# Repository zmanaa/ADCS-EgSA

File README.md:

# ADCS-EgSA
Attitude Determination Control Subsystem project. This project was under supervision of Egyptian Space Agency.

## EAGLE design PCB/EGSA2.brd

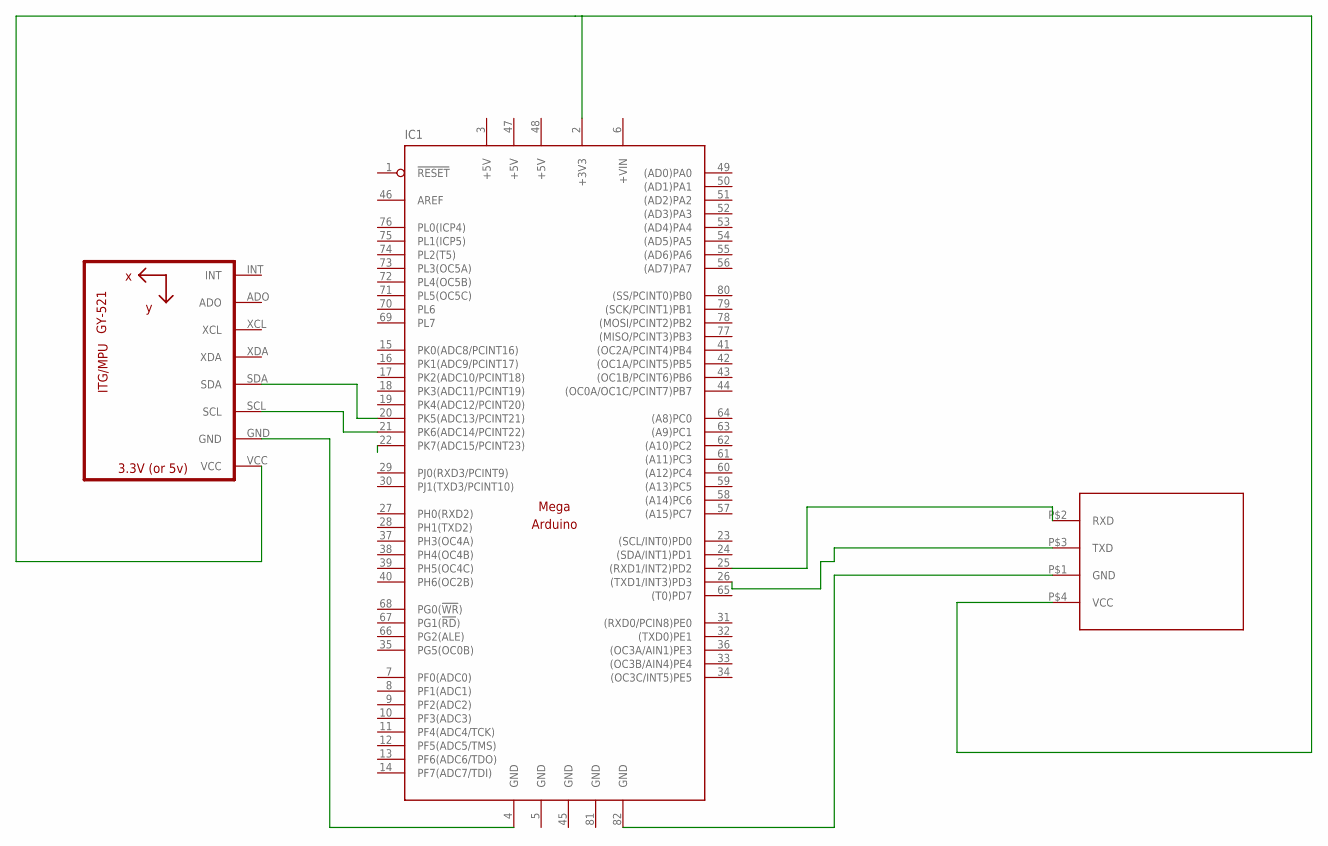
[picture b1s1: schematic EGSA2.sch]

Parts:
IC1: MEGAARDUINO_11; MEGA_ARDUINO_1
U1: GY-521MPU6050; GY-521
U$2: HC-06

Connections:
+5V: IC1.3 (+5V), IC1.47 (+5V), IC1.48 (+5V)
+VIN: IC1.6 (+VIN)
GND: IC1.5 (GND), IC1.45 (GND), IC1.81 (GND)
unnamed: IC1.82 (GND), U$2.P$1 (GND)
unnamed: IC1.21 (PK6(ADC14/PCINT22)), U1.SCL
unnamed: IC1.20 (PK5(ADC13/PCINT21)), U1.SDA
unnamed: IC1.4 (GND), U1.GND
unnamed: IC1.2 (+3V3), U1.VCC, U$2.P$4 (VCC)
unnamed: IC1.25 ((RXD1/INT2)PD2), U$2.P$2 (RXD)
unnamed: IC1.26 ((TXD1/INT3)PD3), U$2.P$3 (TXD)

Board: 2 copper layers, 3 parts (0 on the bottom side), 9 nets, no tracks yet.

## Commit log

2021-09-18 Add CAD files
2021-09-18 Add C++ code
2021-09-19 Add MATLAB GUI
2021-09-19 Add PCB Design
2021-10-05 Add comp. file
